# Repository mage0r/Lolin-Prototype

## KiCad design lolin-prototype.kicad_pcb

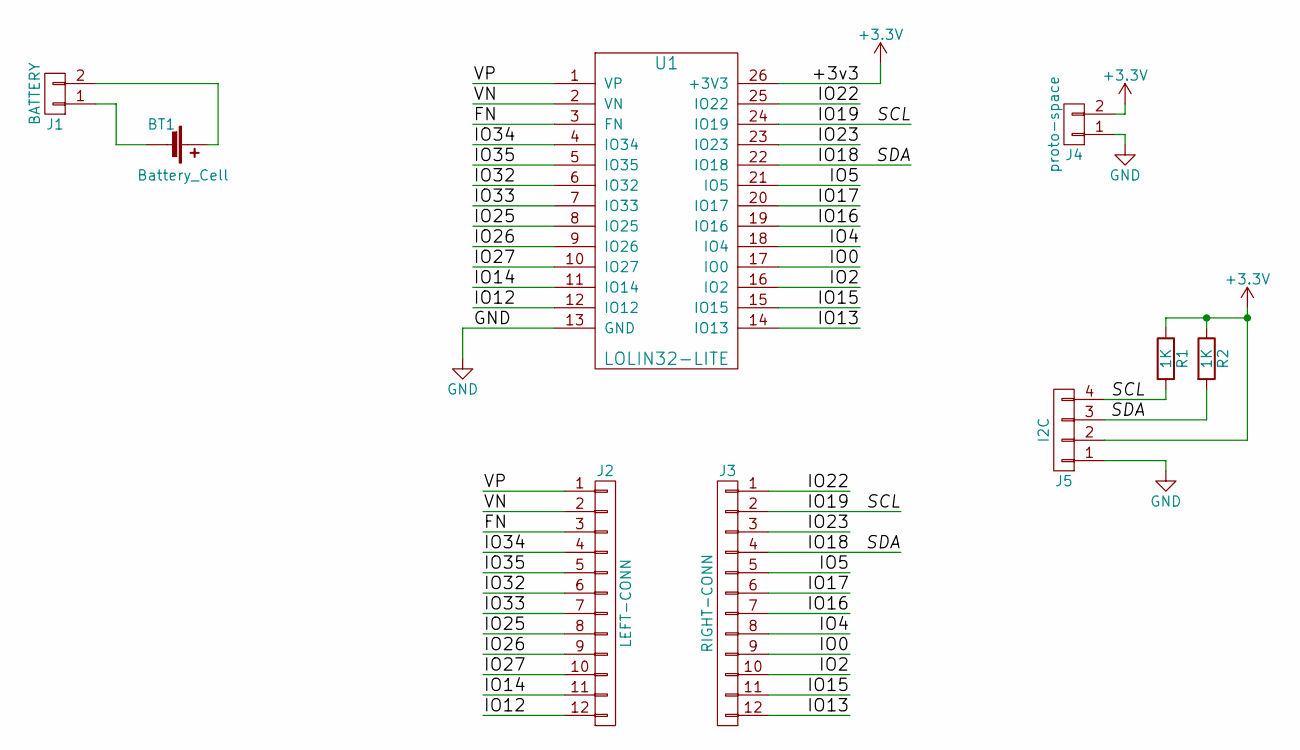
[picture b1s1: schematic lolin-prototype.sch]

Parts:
BT1: Battery_Cell; BH-18650
J1: BATTERY; Pin_Header_Straight_1x02_Pitch2.54mm
J2: LEFT-CONN; Pin_Header_Straight_1x12_Pitch2.54mm
J3: RIGHT-CONN; Pin_Header_Straight_1x12_Pitch2.54mm
J4: proto-space; proto-board
J5: I2C; Pin_Header_Straight_1x04_Pitch2.54mm
R1, R2: 1K; R_0603_HandSoldering
U1: LOLIN32-LITE; lolin32-lite

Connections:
+3V3: J4.2, J5.2, R1.1, R2.1, U1.26 (+3V3)
/FN: J2.3, U1.3 (FN)
/IO0: J3.9, U1.17 (IO0)
/IO2: J3.10, U1.16 (IO2)
/IO4: J3.8, U1.18 (IO4)
/IO5: J3.5, U1.21 (IO5)
/IO12: J2.12, U1.12 (IO12)
/IO13: J3.12, U1.14 (IO13)
/IO14: J2.11, U1.11 (IO14)
/IO15: J3.11, U1.15 (IO15)
/IO16: J3.7, U1.19 (IO16)
/IO17: J3.6, U1.20 (IO17)
/IO18: J3.4, J5.3, R2.2, U1.22 (IO18)
/IO19: J3.2, J5.4, R1.2, U1.24 (IO19)
/IO22: J3.1, U1.25 (IO22)
/IO23: J3.3, U1.23 (IO23)
/IO25: J2.8, U1.8 (IO25)
/IO26: J2.9, U1.9 (IO26)
/IO27: J2.10, U1.10 (IO27)
/IO32: J2.6, U1.6 (IO32)
/IO33: J2.7, U1.7 (IO33)
/IO34: J2.4, U1.4 (IO34)
/IO35: J2.5, U1.5 (IO35)
/VN: J2.2, U1.2 (VN)
/VP: J2.1, U1.1 (VP)
GND: J4.1, J5.1, U1.13 (GND)
unnamed: BT1.1 (+), J1.2
unnamed: BT1.2 (-), J1.1

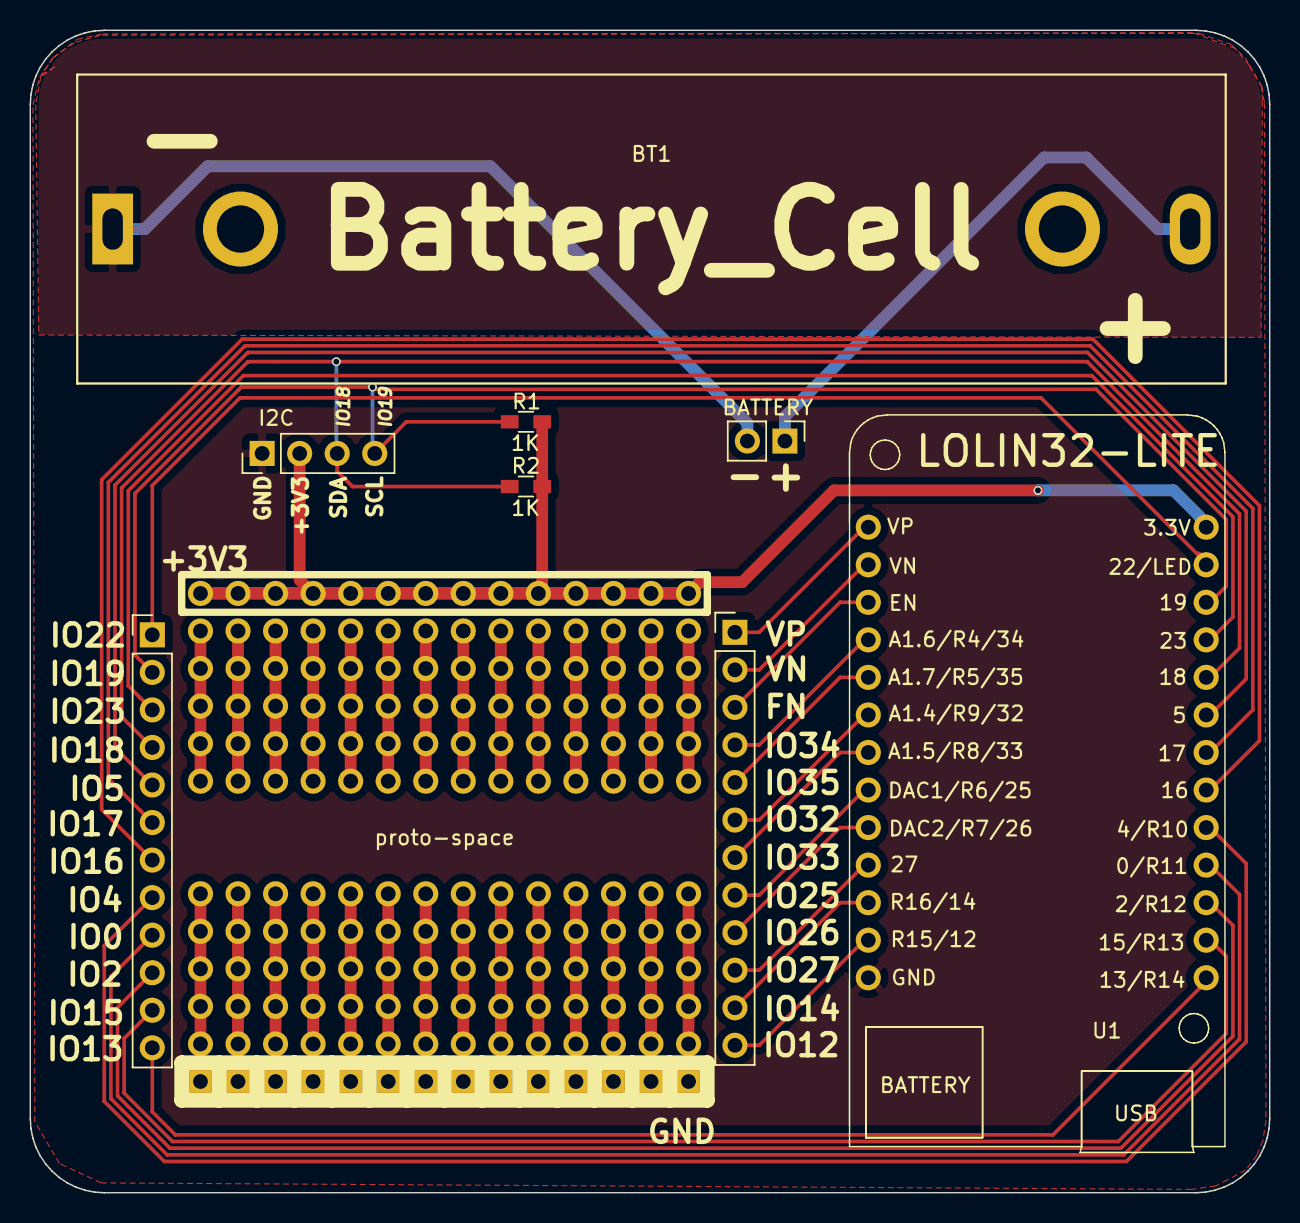
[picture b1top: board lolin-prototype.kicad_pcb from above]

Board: 2 copper layers, 83.8 x 78.6 mm, 9 parts (0 on the bottom side), 28 nets.

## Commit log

2017-10-12 :neckbeard: Added .gitattributes & .gitignore files
2017-10-14 Lolin32-Lite Prototype board
2017-10-14 Trivial updates to make version 1.0
2017-10-26 Updated lolin32-lite and prototyping space footprint
